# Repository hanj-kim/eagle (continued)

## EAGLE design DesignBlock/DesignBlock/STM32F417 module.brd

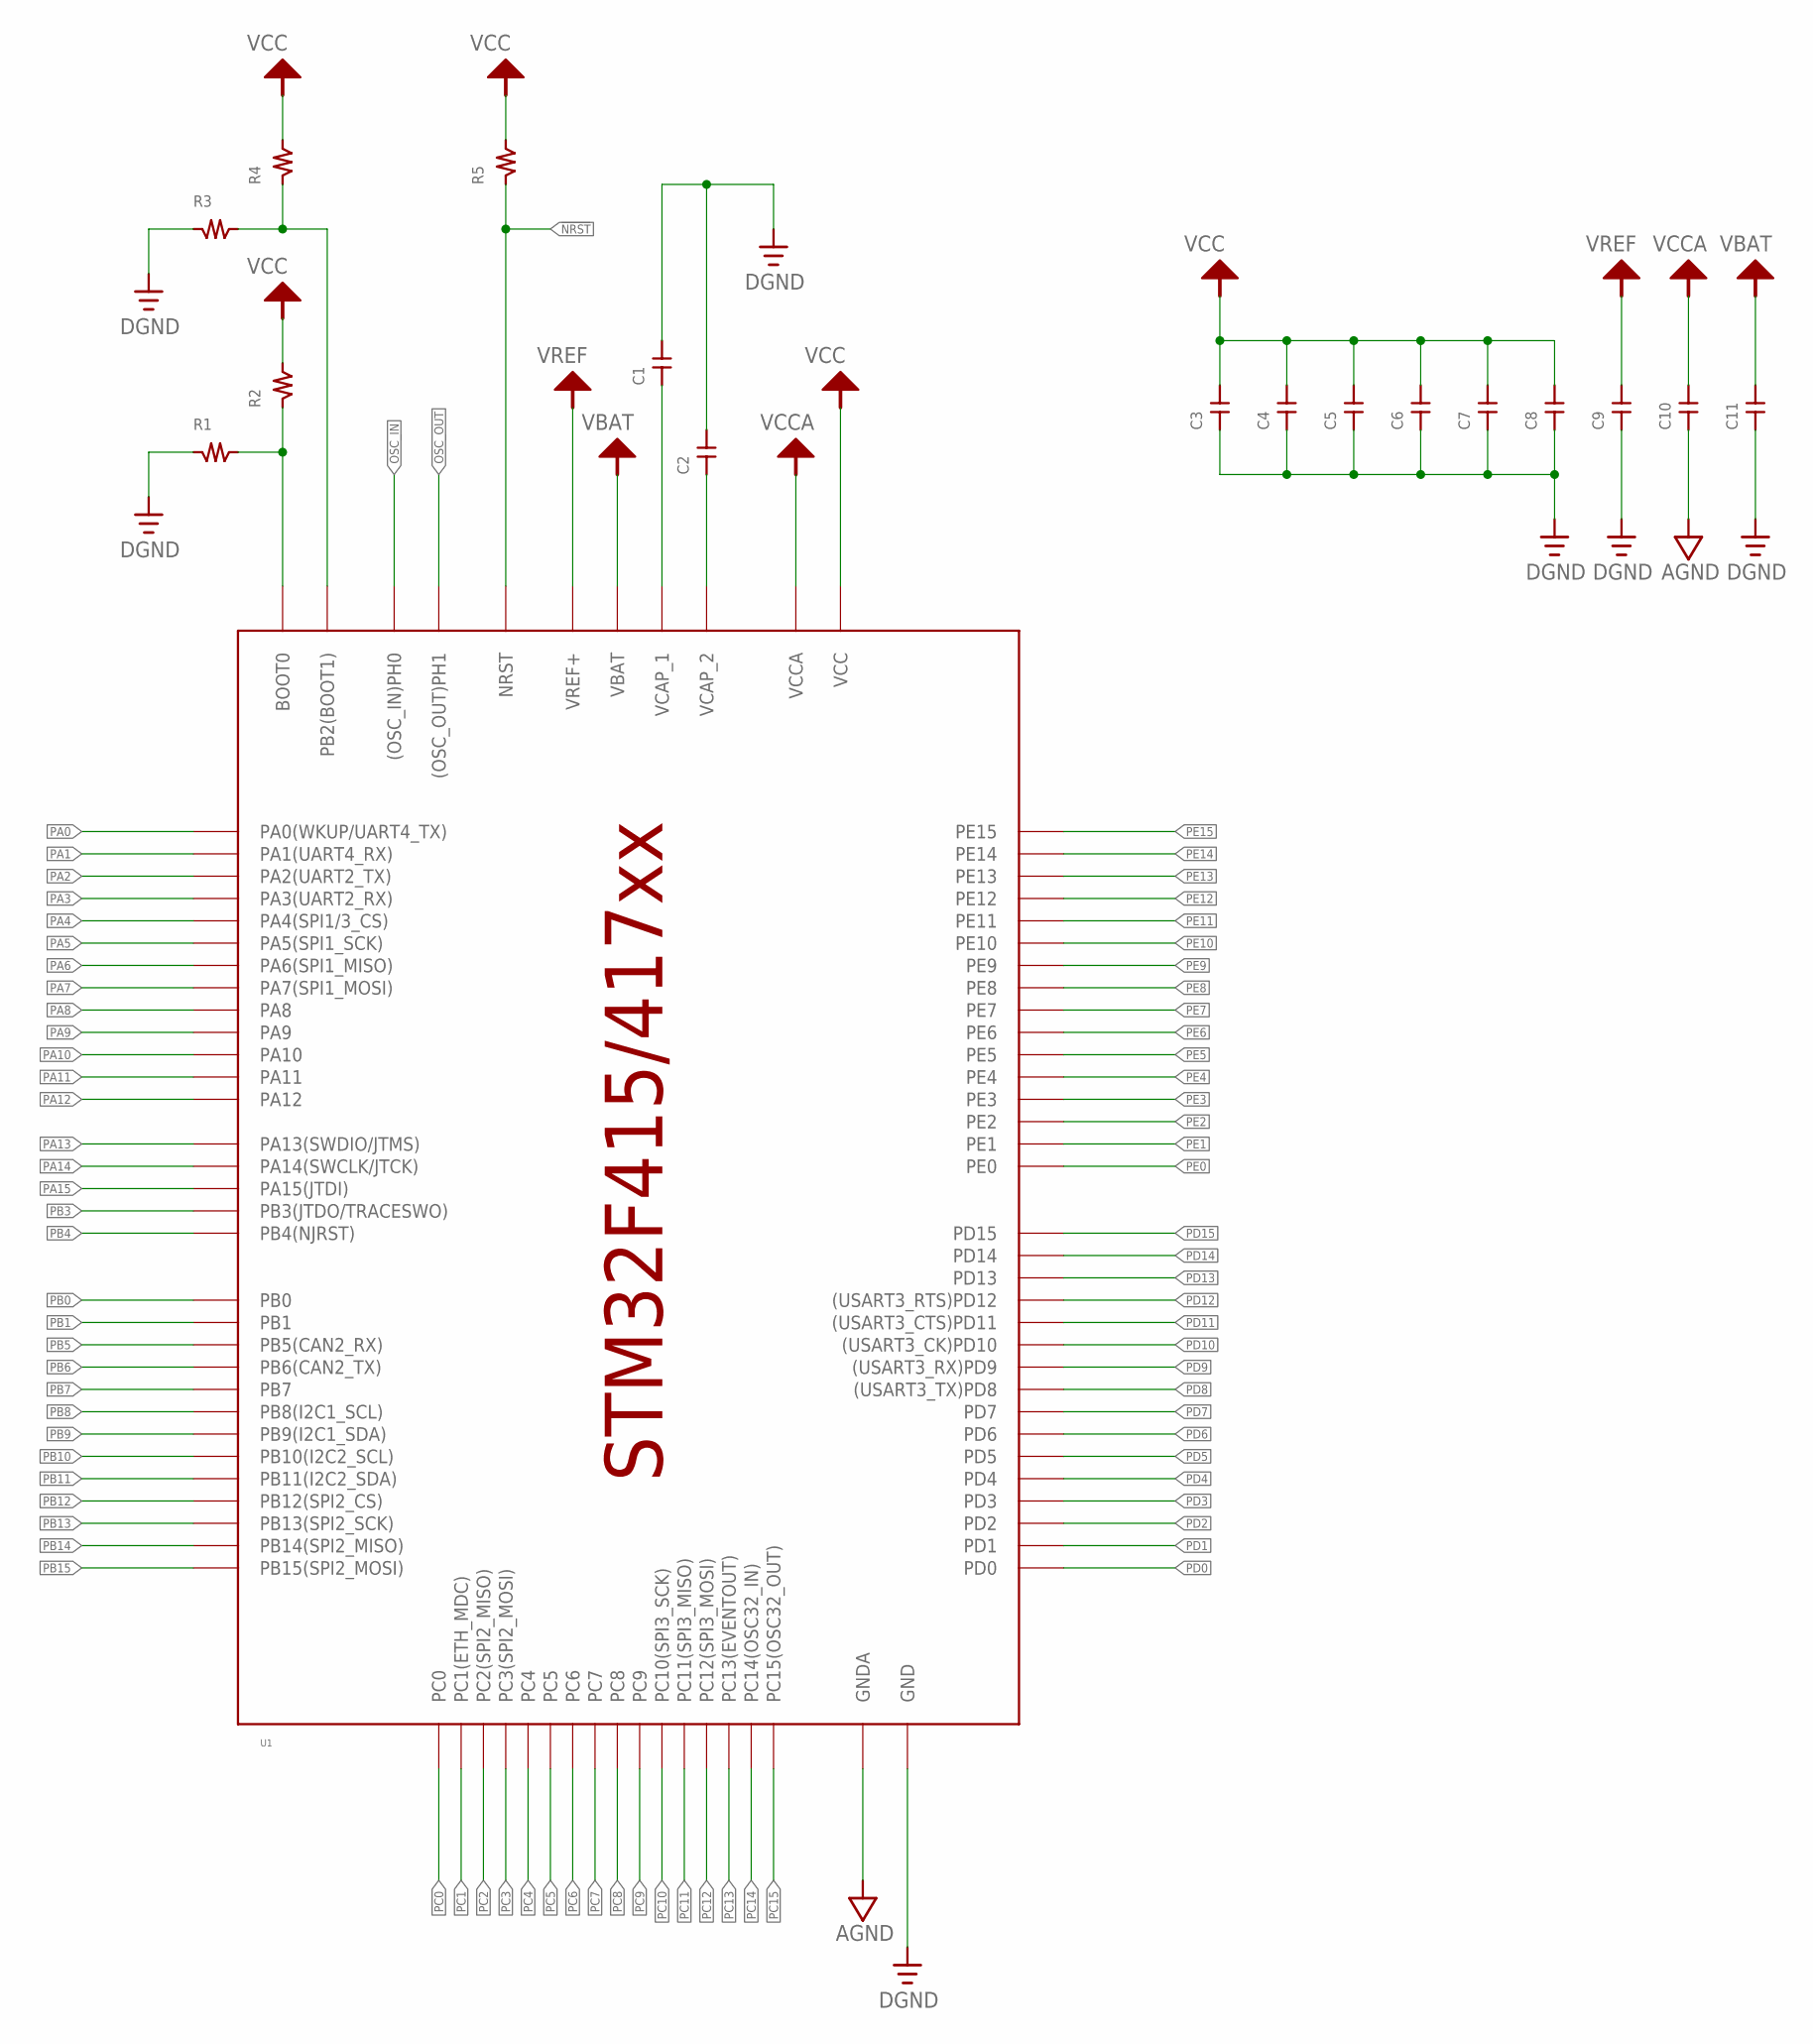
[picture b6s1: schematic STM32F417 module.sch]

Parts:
C1, C2, C3, C4, C5, C6, C7, C8, C9, C10, C11: CAPACITOR_CHIP2012; 2012
R1, R2, R3, R4, R5: RESISTOR_CHIP_2012; 2012
U1: STM32F415/417; LQFP100

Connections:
!NRST: R5.P$1, U1.P$14 (NRST)
AGND: C10.P$1, U1.P$20 (GNDA)
BOOT0: R1.P$2, R2.P$1, U1.P$94 (BOOT0)
BOOT1: R3.P$2, R4.P$1, U1.P$37 (PB2(BOOT1))
DGND: C1.P$2, C2.P$2, C3.P$1, C4.P$1, C5.P$1, C6.P$1, C7.P$1, C8.P$1, C9.P$1, C11.P$1, R1.P$1, R3.P$1, U1.P$10 (GND), U1.P$27 (GND), U1.P$74 (GND), U1.P$99 (GND)
OSC_IN: U1.P$12 ((OSC_IN)PH0)
OSC_OUT: U1.P$13 ((OSC_OUT)PH1)
PA0: U1.P$23 (PA0(WKUP/UART4_TX))
PA1: U1.P$24 (PA1(UART4_RX))
PA2: U1.P$25 (PA2(UART2_TX))
PA3: U1.P$26 (PA3(UART2_RX))
PA4: U1.P$29 (PA4(SPI1/3_CS))
PA5: U1.P$30 (PA5(SPI1_SCK))
PA6: U1.P$31 (PA6(SPI1_MISO))
PA7: U1.P$32 (PA7(SPI1_MOSI))
PA8: U1.P$67 (PA8)
PA9: U1.P$68 (PA9)
PA10: U1.P$69 (PA10)
PA11: U1.P$70 (PA11)
PA12: U1.P$71 (PA12)
PA13: U1.P$72 (PA13(SWDIO/JTMS))
PA14: U1.P$76 (PA14(SWCLK/JTCK))
PA15: U1.P$77 (PA15(JTDI))
PB0: U1.P$35 (PB0)
PB1: U1.P$36 (PB1)
PB3: U1.P$89 (PB3(JTDO/TRACESWO))
PB4: U1.P$90 (PB4(NJRST))
PB5: U1.P$91 (PB5(CAN2_RX))
PB6: U1.P$92 (PB6(CAN2_TX))
PB7: U1.P$93 (PB7)
PB8: U1.P$95 (PB8(I2C1_SCL))
PB9: U1.P$96 (PB9(I2C1_SDA))
PB10: U1.P$47 (PB10(I2C2_SCL))
PB11: U1.P$48 (PB11(I2C2_SDA))
PB12: U1.P$51 (PB12(SPI2_CS))
PB13: U1.P$52 (PB13(SPI2_SCK))
PB14: U1.P$53 (PB14(SPI2_MISO))
PB15: U1.P$54 (PB15(SPI2_MOSI))
PC0: U1.P$15 (PC0)
PC1: U1.P$16 (PC1(ETH_MDC))
PC2: U1.P$17 (PC2(SPI2_MISO))
PC3: U1.P$18 (PC3(SPI2_MOSI))
PC4: U1.P$33 (PC4)
PC5: U1.P$34 (PC5)
PC6: U1.P$63 (PC6)
PC7: U1.P$64 (PC7)
PC8: U1.P$65 (PC8)
PC9: U1.P$66 (PC9)
PC10: U1.P$78 (PC10(SPI3_SCK))
PC11: U1.P$79 (PC11(SPI3_MISO))
PC12: U1.P$80 (PC12(SPI3_MOSI))
PC13: U1.P$7 (PC13(EVENTOUT))
PC14: U1.P$8 (PC14(OSC32_IN))
PC15: U1.P$9 (PC15(OSC32_OUT))
PD0: U1.P$81 (PD0)
PD1: U1.P$82 (PD1)
PD2: U1.P$83 (PD2)
PD3: U1.P$84 (PD3)
PD4: U1.P$85 (PD4)
PD5: U1.P$86 (PD5)
PD6: U1.P$87 (PD6)
PD7: U1.P$88 (PD7)
PD8: U1.P$55 ((USART3_TX)PD8)
PD9: U1.P$56 ((USART3_RX)PD9)
PD10: U1.P$57 ((USART3_CK)PD10)
PD11: U1.P$58 ((USART3_CTS)PD11)
PD12: U1.P$59 ((USART3_RTS)PD12)
PD13: U1.P$60 (PD13)
PD14: U1.P$61 (PD14)
PD15: U1.P$62 (PD15)
PE0: U1.P$97 (PE0)
PE1: U1.P$98 (PE1)
PE2: U1.P$1 (PE2)
PE3: U1.P$2 (PE3)
PE4: U1.P$3 (PE4)
PE5: U1.P$4 (PE5)
PE6: U1.P$5 (PE6)
PE7: U1.P$38 (PE7)
PE8: U1.P$39 (PE8)
PE9: U1.P$40 (PE9)
PE10: U1.P$41 (PE10)
PE11: U1.P$42 (PE11)
PE12: U1.P$43 (PE12)
PE13: U1.P$44 (PE13)
PE14: U1.P$45 (PE14)
PE15: U1.P$46 (PE15)
VBAT: C11.P$2, U1.P$6 (VBAT)
VCAP1: C1.P$1, U1.P$49 (VCAP_1)
VCAP2: C2.P$1, U1.P$73 (VCAP_2)
VCC: C3.P$2, C4.P$2, C5.P$2, C6.P$2, C7.P$2, C8.P$2, R2.P$2, R4.P$2, R5.P$2, U1.P$11 (VCC), U1.P$19 (VCC), U1.P$28 (VCC), U1.P$50 (VCC), U1.P$75 (VCC), U1.P$100 (VCC)
VCCA: C10.P$2, U1.P$22 (VCCA)
VREF: C9.P$2, U1.P$21 (VREF+)

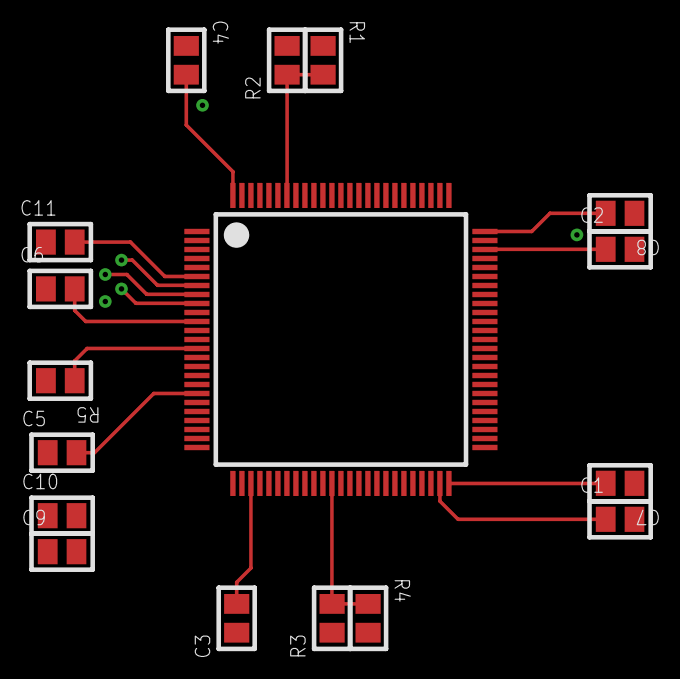
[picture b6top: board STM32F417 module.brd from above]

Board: 2 copper layers, 17 parts (0 on the bottom side), 11 nets.

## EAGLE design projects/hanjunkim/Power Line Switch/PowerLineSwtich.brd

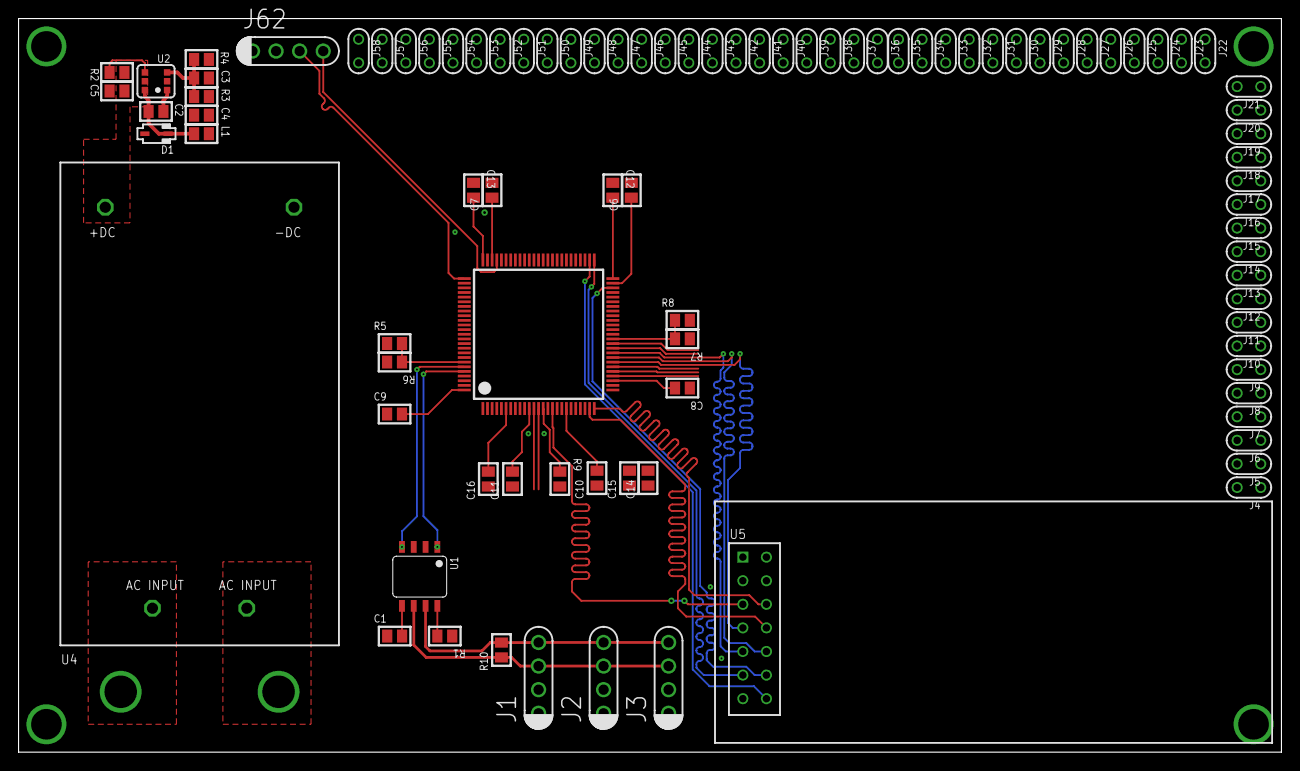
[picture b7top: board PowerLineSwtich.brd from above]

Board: 4 copper layers, 136.0 x 79.0 mm, 92 parts (0 on the bottom side), 32 nets.

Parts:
C1, C15, C16: 100nF; 2012
C2: 22nF; 2012
C3: 100pF; 2012
C4, C5: 22uF; 2012
C6, C7: 2.2uF; 2012
C8: 4.7uF; 2012
C9, C10, C11, C12, C13, C14: 1uF; 2012
D1: SOD323
J1, J2, J3, J62: 4PIN
J4, J5, J6, J7, J8, J9, J10, J11, J12, J13, J14, J15, J16, J17, J18, J19, J20, J21, J22, J23, J24, J25, J26, J27, J28, J29, J30, J31, J32, J33, J34, J35, J36, J37, J38, J39, J40, J41, J42, J43, J44, J45, J46, J47, J48, J49, J50, J51, J52, J53, J54, J55, J56, J57, J58: 2PIN
L1: 2012
R1: 20K; 2012
R2: 100J; 2012
R3: 50K; 2012
R4: 16.2K; 2012
R5, R6, R7, R8, R9: 10K; 2012
R10: 120; 2012
U1: PG-DSO-8
U2: SOT-26
U3: LQFP100
U4: GMSXXXX
U5: 7X2

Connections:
5V: C5.P$2, R2.P$2, U2.P5, U4.P4
!NRST: R9.P$1, U3.P$14
BOOT0: R5.P$2, R6.P$1, U3.P$94
BOOT1: R7.P$2, R8.P$1, U3.P$37
BST: C2.P$1, U2.P1
CAN1_RX: U1.P4, U3.P$95
CAN1_TX: U1.P1, U3.P$96
CANH: J1.P$4, J2.P$4, J3.P$4, R10.P$2, U1.P7
CANL: J1.P$3, J2.P$3, J3.P$3, R10.P$1, U1.P6
CRS_DV: U3.P$32, U5.P7
DGND: C1.P$1, C4.P$1, C5.P$1, C6.P$2, C7.P$2, C8.P$1, C9.P$1, C10.P$1, C11.P$1, C12.P$1, C13.P$1, C14.P$1, C15.P$1, C16.P$1, D1.A, J1.P$1, J2.P$1, J3.P$1, J4.P$2, J5.P$2, J6.P$2, J7.P$2, J8.P$2, J9.P$2, J10.P$2, J11.P$2, J12.P$2, J13.P$2, J14.P$2, J15.P$2, J16.P$2, J17.P$2, J18.P$2, J19.P$2, J20.P$2, J21.P$2, J22.P$2, J23.P$2, J24.P$2, J25.P$2, J26.P$2, J27.P$2, J28.P$2, J29.P$2, J30.P$2, J31.P$2, J32.P$2, J33.P$2, J34.P$2, J35.P$2, J36.P$2, J37.P$2, J38.P$2, J39.P$2, J40.P$2, J41.P$2, J42.P$2, J43.P$2, J44.P$2, J45.P$2, J46.P$2, J47.P$2, J48.P$2, J49.P$2, J50.P$2, J51.P$2, J52.P$2, J53.P$2, J54.P$2, J55.P$2, J56.P$2, J57.P$2, J58.P$2, J62.P$1, R1.P$1, R4.P$1, R5.P$1, R7.P$1, U1.P2, U2.P2, U3.P$10, U3.P$20, U3.P$27, U3.P$74, U3.P$99, U4.P3, U5.P3, U5.P4
EN: R2.P$1, U2.P4
FB: C3.P$1, R3.P$1, R4.P$2, U2.P3
MDC: U3.P$16, U5.P5
MDIO: U3.P$25, U5.P6
unnamed: R1.P$2, U1.P8
unnamed: J4.P$1, J5.P$1, J6.P$1, J7.P$1, J8.P$1, J9.P$1, J10.P$1, J11.P$1, J12.P$1, J13.P$1, J14.P$1, J15.P$1, J16.P$1, J17.P$1, J18.P$1, J19.P$1, J20.P$1, J21.P$1, J22.P$1, J23.P$1, J24.P$1, J25.P$1, J26.P$1, J27.P$1, J28.P$1, J29.P$1, J30.P$1, J31.P$1, J32.P$1, J33.P$1, J34.P$1, J35.P$1, J36.P$1, J37.P$1, J38.P$1, J39.P$1, J40.P$1, J41.P$1, J42.P$1, J43.P$1, J44.P$1, J45.P$1, J46.P$1, J47.P$1, J48.P$1, J49.P$1, J50.P$1, J51.P$1, J52.P$1, J53.P$1, J54.P$1, J55.P$1, J56.P$1, J57.P$1, J58.P$1
RXD0: U3.P$33, U5.P10
RXD1: U3.P$34, U5.P9
R_RXCLK: U3.P$24, U5.P8
SW: C2.P$2, D1.K, L1.P$1, U2.P6
SWCLK: J62.P$3, U3.P$76
SWDIO: J62.P$4, U3.P$72
TXD0: U3.P$51, U5.P11
TXD1: U3.P$52, U5.P14
TX_EN: U3.P$48, U5.P12
VBAT: C16.P$2, U3.P$6
VCAP1: C6.P$1, U3.P$49
VCAP2: C7.P$1, U3.P$73
VCC: C1.P$2, C8.P$2, C9.P$2, C10.P$2, C11.P$2, C12.P$2, C13.P$2, C15.P$2, J1.P$2, J2.P$2, J3.P$2, J62.P$2, R6.P$2, R8.P$2, R9.P$2, U1.P3, U1.P5, U3.P$11, U3.P$19, U3.P$22, U3.P$28, U3.P$50, U3.P$75, U3.P$100, U5.P1, U5.P2
VOUT: C3.P$2, C4.P$2, L1.P$2, R3.P$2
VREF: C14.P$2, U3.P$21

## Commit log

2018-10-28 # Library Upload
2018-10-28 #2 update gitignore
2018-10-28 update connector lib
2018-12-03 modify gitignore & project file
2018-12-03 edit gitignore
